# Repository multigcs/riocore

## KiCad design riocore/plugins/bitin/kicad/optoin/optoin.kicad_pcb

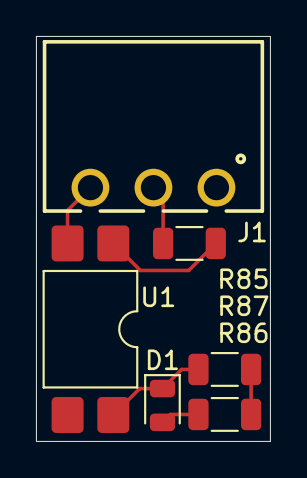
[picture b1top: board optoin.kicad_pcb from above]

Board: 2 copper layers, 13.0 x 22.5 mm, 6 parts (0 on the bottom side), 6 nets.

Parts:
D1: LED; LED_0805_2012Metric
J1: opto_in; 691322110003
R85: 3k3; R_1206_3216Metric
R86: 560; R_1206_3216Metric
R87: 1k; R_1206_3216Metric
U1: LTV-817S; SMDIP-4_W9.53mm

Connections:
+3V3: R86.1, R87.1
/bit: D1.1 (K), R87.2, U1.4
F_GND: J1.3, U1.2
unnamed: D1.2 (A), R86.2
unnamed: J1.2, R85.2
unnamed: R85.1, U1.1

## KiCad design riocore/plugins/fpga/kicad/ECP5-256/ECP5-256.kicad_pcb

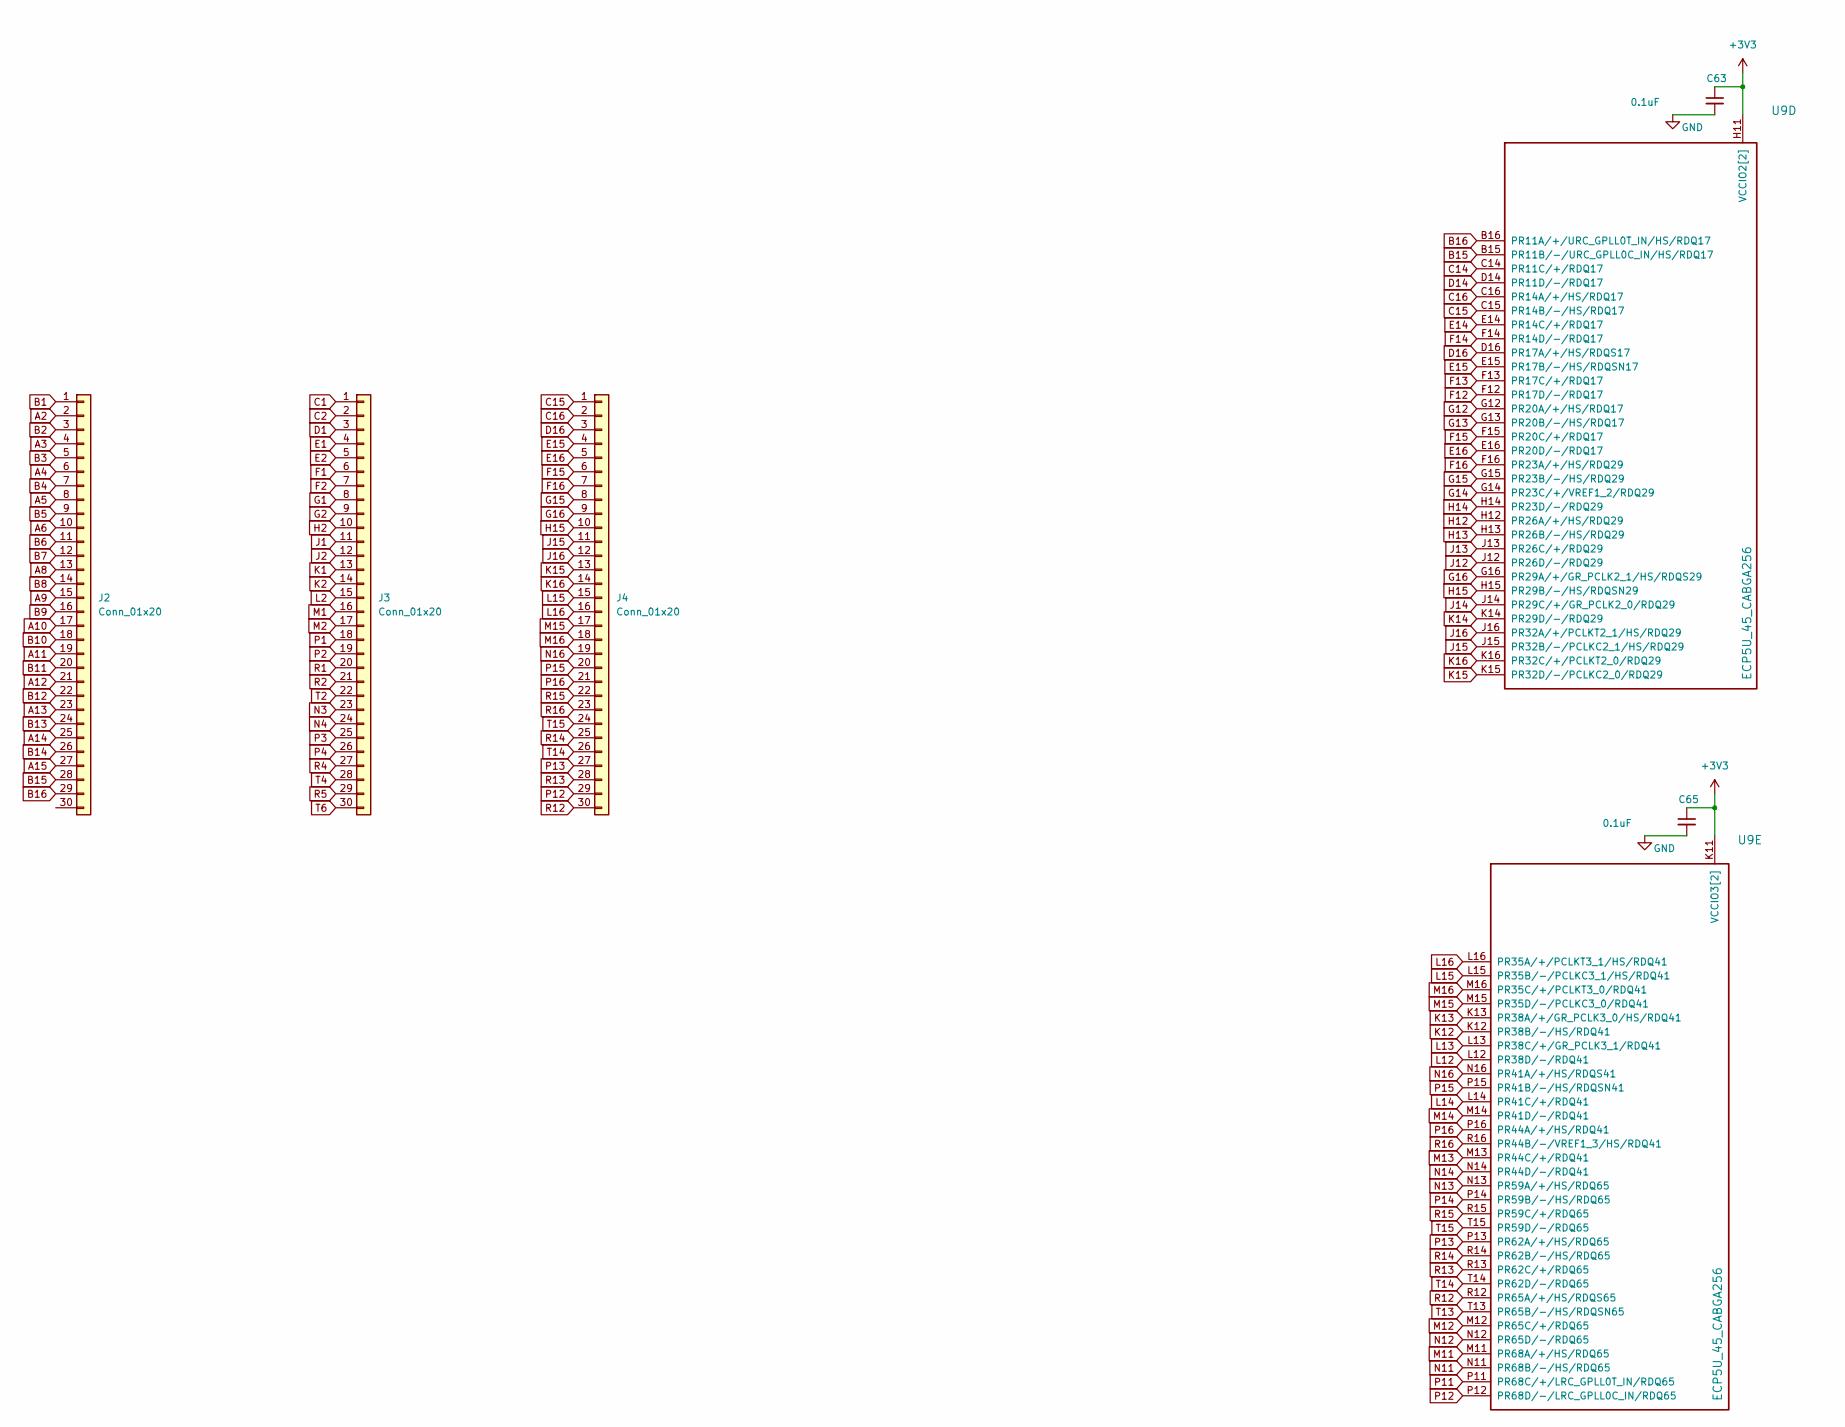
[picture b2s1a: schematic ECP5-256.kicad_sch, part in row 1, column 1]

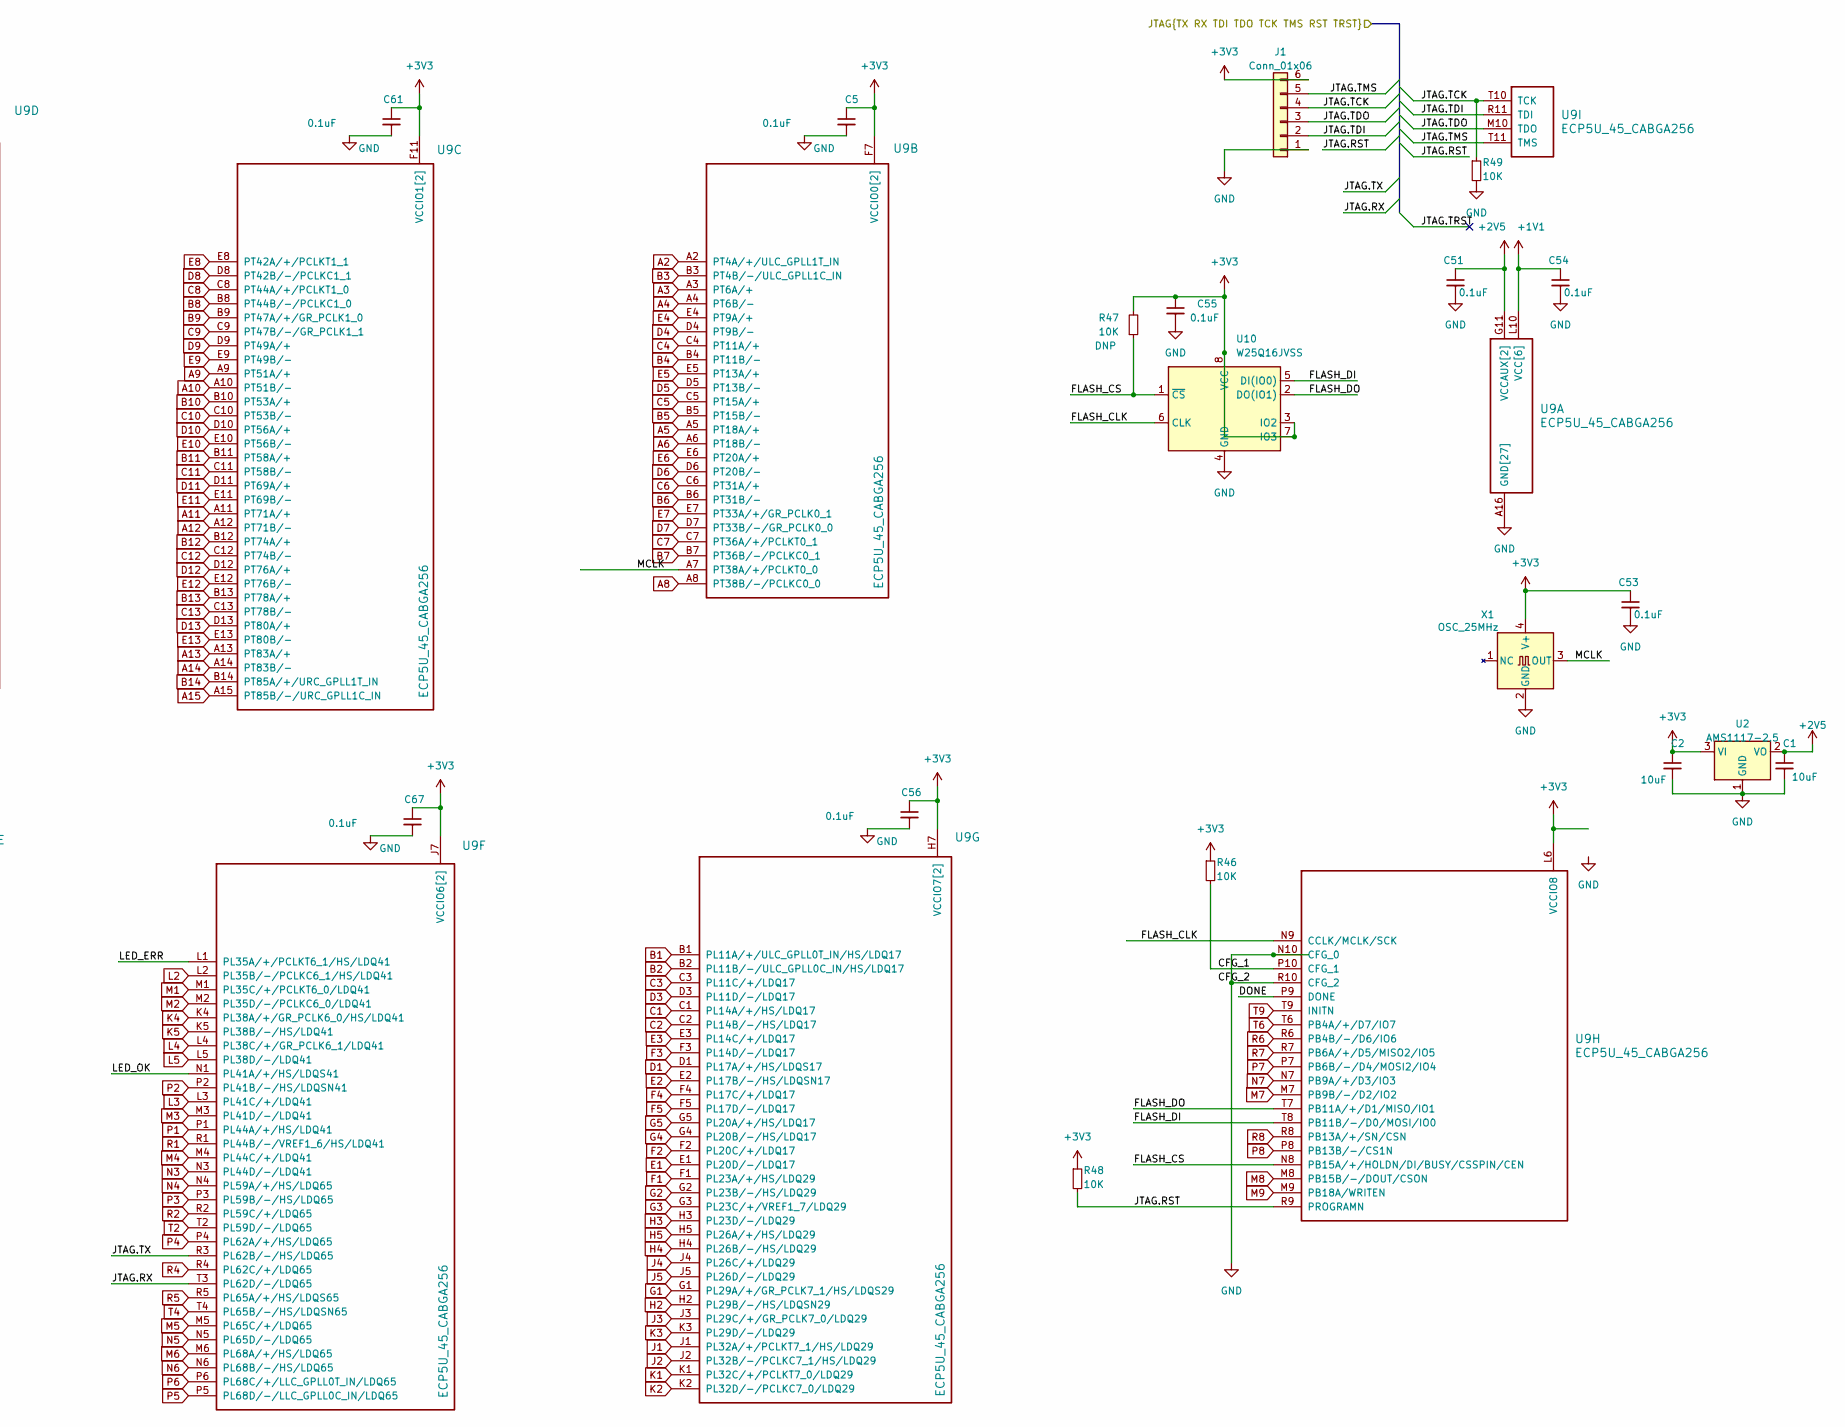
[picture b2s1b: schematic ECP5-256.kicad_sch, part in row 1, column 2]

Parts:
C1, C2: 10uF; C_0805_2012Metric; LCSC# C56392
C5, C51, C53, C54, C56, C61, C63, C65, C67: 0.1uF; C_0805_2012Metric; LCSC# C56392
C55: 0.1uF; C_0805_2012Metric; MPN CC0603KRX7R9BB104; LCSC# C14663
J1: Conn_01x06; PinHeader_1x06_P2.54mm_Vertical
J2, J3, J4: Conn_01x20; PinHeader_1x30_P1.27mm_Vertical
R46, R48, R49: 10K; R_0603_1608Metric; LCSC# C98220
R47: 10K; R_0603_1608Metric; MPN RC0603FR-0710KL; LCSC# C98220
U2: AMS1117-2.5; SOT-223-3_TabPin2
U9: ECP5U_45_CABGA256; BGA-256_14.0x14.0mm_Layout16x16_P0.8mm_Ball0.45mm_Pad0.32mm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; MPN LFE5U-12F-6BG256C; LCSC# C1550762
U10: W25Q16JVSS; SOIC-8_5.3x5.3mm_P1.27mm; MPN W25Q16JVSSIQ; LCSC# C82317
X1: OSC_25MHz; Oscillator_SMD_EuroQuartz_XO32-4Pin_3.2x2.5mm; MPN OT322525MJBA4SL; LCSC# C669088

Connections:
+1V1: C54.1, U9.G6 (VCC[6]), U9.G7 (VCC[6]), U9.G9 (VCC[6]), U9.L8 (VCC[6]), U9.L9 (VCC[6]), U9.L10 (VCC[6])
+2V5: C1.1, C51.1, U2.2 (VO), U9.G11 (VCCAUX[2]), U9.L7 (VCCAUX[2])
+3V3: C2.1, C5.1, C53.1, C55.1, C56.1, C61.1, C63.1, C65.1, C67.1, J1.6, R46.1, R47.2, R48.1, U2.3 (VI), U9.F6 (VCCIO0[2]), U9.F7 (VCCIO0[2]), U9.F10 (VCCIO1[2]), U9.F11 (VCCIO1[2]), U9.H6 (VCCIO7[2]), U9.H7 (VCCIO7[2]), U9.H11 (VCCIO2[2]), U9.J6 (VCCIO6[2]), U9.J7 (VCCIO6[2]), U9.J11 (VCCIO2[2]), U9.K11 (VCCIO3[2]), U9.L6 (VCCIO8), U9.L11 (VCCIO3[2]), U10.3 (IO2), U10.7 (IO3), U10.8 (VCC), X1.4 (V+)
/CFG_1: R46.2, U9.P10 (CFG_1)
/DONE: U9.P9 (DONE)
/FLASH_CLK: U9.N9 (CCLK/MCLK/SCK), U10.6 (CLK)
/FLASH_CS: R47.1, U9.N8 (PB15A/+/HOLDN/DI/BUSY/CSSPIN/CEN), U10.1 (~CS)
/FLASH_DI: U9.T8 (PB11B/-/D0/MOSI/IO0), U10.5 (DI(IO0))
/FLASH_DO: U9.T7 (PB11A/+/D1/MISO/IO1), U10.2 (DO(IO1))
/JTAG.RST: R48.2, U9.R9 (PROGRAMN)
/JTAG.RX: U9.T3 (PL62D/-/LDQ65)
/JTAG.TCK: J1.4, R49.1, U9.T10 (TCK)
/JTAG.TDI: J1.2, U9.R11 (TDI)
/JTAG.TDO: J1.3, U9.M10 (TDO)
/JTAG.TMS: J1.5, U9.T11 (TMS)
/JTAG.TX: U9.R3 (PL62B/-/HS/LDQ65)
/LED_ERR: U9.L1 (PL35A/+/PCLKT6_1/HS/LDQ41)
/LED_OK: U9.N1 (PL41A/+/HS/LDQS41)
/MCLK: U9.A7 (PT38A/+/PCLKT0_0), X1.3 (OUT)
A2: J2.2, U9.A2 (PT4A/+/ULC_GPLL1T_IN)
A3: J2.4, U9.A3 (PT6A/+)
A4: J2.6, U9.A4 (PT6B/-)
A5: J2.8, U9.A5 (PT18A/+)
A6: J2.10, U9.A6 (PT18B/-)
A8: J2.13, U9.A8 (PT38B/-/PCLKC0_0)
A9: J2.15, U9.A9 (PT51A/+)
A10: J2.17, U9.A10 (PT51B/-)
A11: J2.19, U9.A11 (PT71A/+)
A12: J2.21, U9.A12 (PT71B/-)
A13: J2.23, U9.A13 (PT83A/+)
A14: J2.25, U9.A14 (PT83B/-)
A15: J2.27, U9.A15 (PT85B/-/URC_GPLL1C_IN)
B1: J2.1, U9.B1 (PL11A/+/ULC_GPLL0T_IN/HS/LDQ17)
B2: J2.3, U9.B2 (PL11B/-/ULC_GPLL0C_IN/HS/LDQ17)
B3: J2.5, U9.B3 (PT4B/-/ULC_GPLL1C_IN)
B4: J2.7, U9.B4 (PT11B/-)
B5: J2.9, U9.B5 (PT15B/-)
B6: J2.11, U9.B6 (PT31B/-)
B7: J2.12, U9.B7 (PT36B/-/PCLKC0_1)
B8: J2.14, U9.B8 (PT44B/-/PCLKC1_0)
B9: J2.16, U9.B9 (PT47A/+/GR_PCLK1_0)
B10: J2.18, U9.B10 (PT53A/+)
B11: J2.20, U9.B11 (PT58A/+)
B12: J2.22, U9.B12 (PT74A/+)
B13: J2.24, U9.B13 (PT78A/+)
B14: J2.26, U9.B14 (PT85A/+/URC_GPLL1T_IN)
B15: J2.28, U9.B15 (PR11B/-/URC_GPLL0C_IN/HS/RDQ17)
B16: J2.29, U9.B16 (PR11A/+/URC_GPLL0T_IN/HS/RDQ17)
C1: J3.1, U9.C1 (PL14A/+/HS/LDQ17)
C2: J3.2, U9.C2 (PL14B/-/HS/LDQ17)
C3: U9.C3 (PL11C/+/LDQ17)
C4: U9.C4 (PT11A/+)
C5: U9.C5 (PT15A/+)
C6: U9.C6 (PT31A/+)
C7: U9.C7 (PT36A/+/PCLKT0_1)
C8: U9.C8 (PT44A/+/PCLKT1_0)
C9: U9.C9 (PT47B/-/GR_PCLK1_1)
C10: U9.C10 (PT53B/-)
C11: U9.C11 (PT58B/-)
C12: U9.C12 (PT74B/-)
C13: U9.C13 (PT78B/-)
C14: U9.C14 (PR11C/+/RDQ17)
C15: J4.1, U9.C15 (PR14B/-/HS/RDQ17)
C16: J4.2, U9.C16 (PR14A/+/HS/RDQ17)
D1: J3.3, U9.D1 (PL17A/+/HS/LDQS17)
D3: U9.D3 (PL11D/-/LDQ17)
D4: U9.D4 (PT9B/-)
D5: U9.D5 (PT13B/-)
D6: U9.D6 (PT20B/-)
D7: U9.D7 (PT33B/-/GR_PCLK0_0)
D8: U9.D8 (PT42B/-/PCLKC1_1)
D9: U9.D9 (PT49A/+)
D10: U9.D10 (PT56A/+)
D11: U9.D11 (PT69A/+)
D12: U9.D12 (PT76A/+)
D13: U9.D13 (PT80A/+)
D14: U9.D14 (PR11D/-/RDQ17)
D16: J4.3, U9.D16 (PR17A/+/HS/RDQS17)
E1: J3.4, U9.E1 (PL20D/-/LDQ17)
E2: J3.5, U9.E2 (PL17B/-/HS/LDQSN17)
E3: U9.E3 (PL14C/+/LDQ17)
E4: U9.E4 (PT9A/+)
E5: U9.E5 (PT13A/+)
E6: U9.E6 (PT20A/+)
E7: U9.E7 (PT33A/+/GR_PCLK0_1)
E8: U9.E8 (PT42A/+/PCLKT1_1)
E9: U9.E9 (PT49B/-)
E10: U9.E10 (PT56B/-)
E11: U9.E11 (PT69B/-)
E12: U9.E12 (PT76B/-)
E13: U9.E13 (PT80B/-)
E14: U9.E14 (PR14C/+/RDQ17)
E15: J4.4, U9.E15 (PR17B/-/HS/RDQSN17)
E16: J4.5, U9.E16 (PR20D/-/RDQ17)
F1: J3.6, U9.F1 (PL23A/+/HS/LDQ29)
F2: J3.7, U9.F2 (PL20C/+/LDQ17)
F3: U9.F3 (PL14D/-/LDQ17)
F4: U9.F4 (PL17C/+/LDQ17)
F5: U9.F5 (PL17D/-/LDQ17)
F12: U9.F12 (PR17D/-/RDQ17)
F13: U9.F13 (PR17C/+/RDQ17)
F14: U9.F14 (PR14D/-/RDQ17)
F15: J4.6, U9.F15 (PR20C/+/RDQ17)
F16: J4.7, U9.F16 (PR23A/+/HS/RDQ29)
G1: J3.8, U9.G1 (PL29A/+/GR_PCLK7_1/HS/LDQS29)
G2: J3.9, U9.G2 (PL23B/-/HS/LDQ29)
G3: U9.G3 (PL23C/+/VREF1_7/LDQ29)
G4: U9.G4 (PL20B/-/HS/LDQ17)
G5: U9.G5 (PL20A/+/HS/LDQ17)
G12: U9.G12 (PR20A/+/HS/RDQ17)
G13: U9.G13 (PR20B/-/HS/RDQ17)
G14: U9.G14 (PR23C/+/VREF1_2/RDQ29)
G15: J4.8, U9.G15 (PR23B/-/HS/RDQ29)
G16: J4.9, U9.G16 (PR29A/+/GR_PCLK2_1/HS/RDQS29)
GND: C1.2, C2.2, C5.2, C51.2, C53.2, C54.2, C55.2, C56.2, C61.2, C63.2, C65.2, C67.2, J1.1, R49.2, U2.1 (GND), U9.A1 (GND[27]), U9.A16 (GND[27]), U9.D2 (GND[27]), U9.D15 (GND[27]), U9.F8 (GND[27]), U9.F9 (GND[27]), U9.G8 (GND[27]), U9.G10 (GND[27]), U9.H1 (GND[27]), U9.H8 (GND[27]), U9.H9 (GND[27]), U9.H10 (GND[27]), U9.H16 (GND[27]), U9.J8 (GND[27]), U9.J9 (GND[27]), U9.J10 (GND[27]), U9.K6 (GND[27]), U9.K7 (GND[27]), U9.K8 (GND[27]), U9.K9 (GND[27]), U9.K10 (GND[27]), U9.N2 (GND[27]), U9.N10 (CFG_0), U9.N15 (GND[27]), U9.R10 (CFG_2), U9.T1 (GND[27]), U9.T5 (GND[27]), U9.T12 (GND[27]), U9.T16 (GND[27]), U10.4 (GND), X1.2 (GND)
H2: J3.10, U9.H2 (PL29B/-/HS/LDQSN29)
H3: U9.H3 (PL23D/-/LDQ29)
H4: U9.H4 (PL26B/-/HS/LDQ29)
H5: U9.H5 (PL26A/+/HS/LDQ29)
H12: U9.H12 (PR26A/+/HS/RDQ29)
H13: U9.H13 (PR26B/-/HS/RDQ29)
H14: U9.H14 (PR23D/-/RDQ29)
H15: J4.10, U9.H15 (PR29B/-/HS/RDQSN29)
J1: J3.11, U9.J1 (PL32A/+/PCLKT7_1/HS/LDQ29)
J2: J3.12, U9.J2 (PL32B/-/PCLKC7_1/HS/LDQ29)
J3: U9.J3 (PL29C/+/GR_PCLK7_0/LDQ29)
J4: U9.J4 (PL26C/+/LDQ29)
J5: U9.J5 (PL26D/-/LDQ29)
J12: U9.J12 (PR26D/-/RDQ29)
J13: U9.J13 (PR26C/+/RDQ29)
J14: U9.J14 (PR29C/+/GR_PCLK2_0/RDQ29)
J15: J4.11, U9.J15 (PR32B/-/PCLKC2_1/HS/RDQ29)
J16: J4.12, U9.J16 (PR32A/+/PCLKT2_1/HS/RDQ29)
K1: J3.13, U9.K1 (PL32C/+/PCLKT7_0/LDQ29)
K2: J3.14, U9.K2 (PL32D/-/PCLKC7_0/LDQ29)
K3: U9.K3 (PL29D/-/LDQ29)
K4: U9.K4 (PL38A/+/GR_PCLK6_0/HS/LDQ41)
K5: U9.K5 (PL38B/-/HS/LDQ41)
K12: U9.K12 (PR38B/-/HS/RDQ41)
K13: U9.K13 (PR38A/+/GR_PCLK3_0/HS/RDQ41)
K14: U9.K14 (PR29D/-/RDQ29)
K15: J4.13, U9.K15 (PR32D/-/PCLKC2_0/RDQ29)
K16: J4.14, U9.K16 (PR32C/+/PCLKT2_0/RDQ29)
L2: J3.15, U9.L2 (PL35B/-/PCLKC6_1/HS/LDQ41)
L3: U9.L3 (PL41C/+/LDQ41)
L4: U9.L4 (PL38C/+/GR_PCLK6_1/LDQ41)
L5: U9.L5 (PL38D/-/LDQ41)
L12: U9.L12 (PR38D/-/RDQ41)
L13: U9.L13 (PR38C/+/GR_PCLK3_1/RDQ41)
L14: U9.L14 (PR41C/+/RDQ41)
L15: J4.15, U9.L15 (PR35B/-/PCLKC3_1/HS/RDQ41)
L16: J4.16, U9.L16 (PR35A/+/PCLKT3_1/HS/RDQ41)
M1: J3.16, U9.M1 (PL35C/+/PCLKT6_0/LDQ41)
M2: J3.17, U9.M2 (PL35D/-/PCLKC6_0/LDQ41)
M3: U9.M3 (PL41D/-/LDQ41)
M4: U9.M4 (PL44C/+/LDQ41)
M5: U9.M5 (PL65C/+/LDQ65)
M6: U9.M6 (PL68A/+/HS/LDQ65)
M7: U9.M7 (PB9B/-/D2/IO2)
M8: U9.M8 (PB15B/-/DOUT/CSON)
M9: U9.M9 (PB18A/WRITEN)
M11: U9.M11 (PR68A/+/HS/RDQ65)
M12: U9.M12 (PR65C/+/RDQ65)
M13: U9.M13 (PR44C/+/RDQ41)
M14: U9.M14 (PR41D/-/RDQ41)
M15: J4.17, U9.M15 (PR35D/-/PCLKC3_0/RDQ41)
M16: J4.18, U9.M16 (PR35C/+/PCLKT3_0/RDQ41)
N3: J3.23, U9.N3 (PL44D/-/LDQ41)
N4: J3.24, U9.N4 (PL59A/+/HS/LDQ65)
N5: U9.N5 (PL65D/-/LDQ65)
N6: U9.N6 (PL68B/-/HS/LDQ65)
N7: U9.N7 (PB9A/+/D3/IO3)
N11: U9.N11 (PR68B/-/HS/RDQ65)
N12: U9.N12 (PR65D/-/RDQ65)
N13: U9.N13 (PR59A/+/HS/RDQ65)
N14: U9.N14 (PR44D/-/RDQ41)
N16: J4.19, U9.N16 (PR41A/+/HS/RDQS41)
P1: J3.18, U9.P1 (PL44A/+/HS/LDQ41)
P2: J3.19, U9.P2 (PL41B/-/HS/LDQSN41)
P3: J3.25, U9.P3 (PL59B/-/HS/LDQ65)
P4: J3.26, U9.P4 (PL62A/+/HS/LDQ65)
P5: U9.P5 (PL68D/-/LLC_GPLL0C_IN/LDQ65)
P6: U9.P6 (PL68C/+/LLC_GPLL0T_IN/LDQ65)
P7: U9.P7 (PB6B/-/D4/MOSI2/IO4)
P8: U9.P8 (PB13B/-/CS1N)
P11: U9.P11 (PR68C/+/LRC_GPLL0T_IN/RDQ65)
P12: J4.29, U9.P12 (PR68D/-/LRC_GPLL0C_IN/RDQ65)
P13: J4.27, U9.P13 (PR62A/+/HS/RDQ65)
P14: U9.P14 (PR59B/-/HS/RDQ65)
P15: J4.20, U9.P15 (PR41B/-/HS/RDQSN41)
P16: J4.21, U9.P16 (PR44A/+/HS/RDQ41)
R1: J3.20, U9.R1 (PL44B/-/VREF1_6/HS/LDQ41)
R2: J3.21, U9.R2 (PL59C/+/LDQ65)
R4: J3.27, U9.R4 (PL62C/+/LDQ65)
R5: J3.29, U9.R5 (PL65A/+/HS/LDQS65)
R6: U9.R6 (PB4B/-/D6/IO6)
R7: U9.R7 (PB6A/+/D5/MISO2/IO5)
R8: U9.R8 (PB13A/+/SN/CSN)
R12: J4.30, U9.R12 (PR65A/+/HS/RDQS65)
R13: J4.28, U9.R13 (PR62C/+/RDQ65)
R14: J4.25, U9.R14 (PR62B/-/HS/RDQ65)
R15: J4.22, U9.R15 (PR59C/+/RDQ65)
R16: J4.23, U9.R16 (PR44B/-/VREF1_3/HS/RDQ41)
T2: J3.22, U9.T2 (PL59D/-/LDQ65)
T4: J3.28, U9.T4 (PL65B/-/HS/LDQSN65)
T6: J3.30, U9.T6 (PB4A/+/D7/IO7)
T9: U9.T9 (INITN)
T13: U9.T13 (PR65B/-/HS/RDQSN65)
T14: J4.26, U9.T14 (PR62D/-/RDQ65)
T15: J4.24, U9.T15 (PR59D/-/RDQ65)

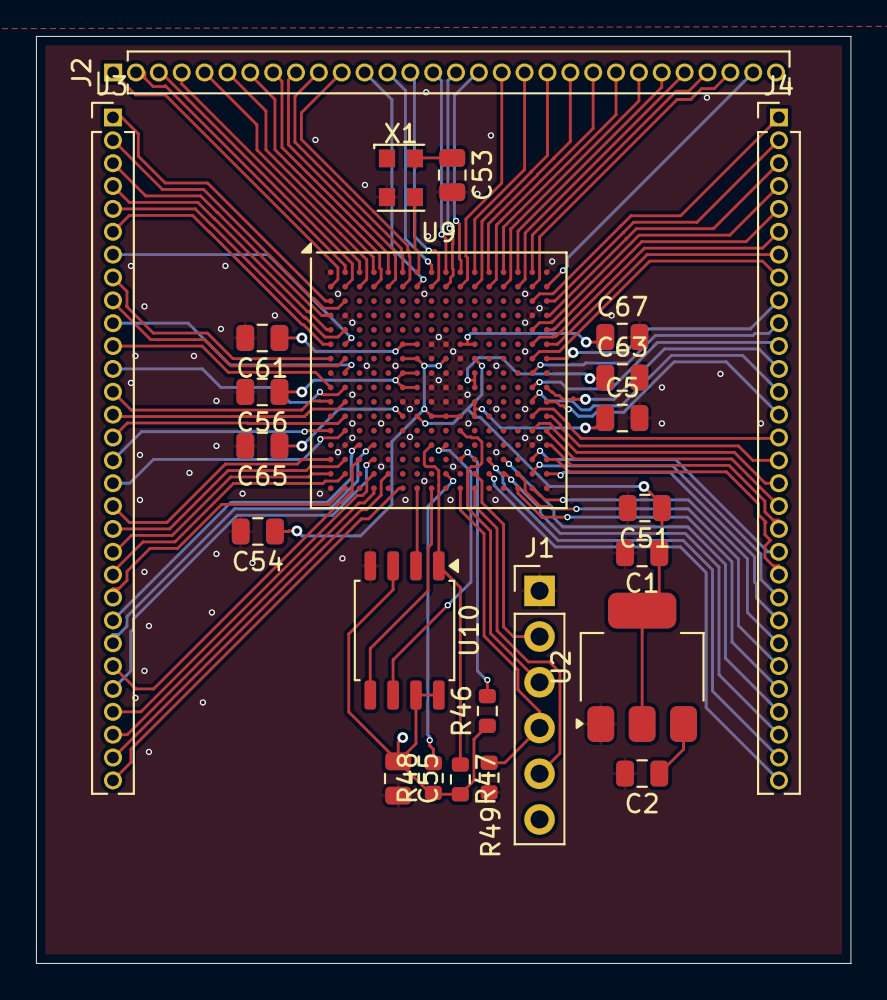
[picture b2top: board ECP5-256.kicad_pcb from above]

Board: 2 copper layers, 45.2 x 51.5 mm, 24 parts (0 on the bottom side), 104 nets.

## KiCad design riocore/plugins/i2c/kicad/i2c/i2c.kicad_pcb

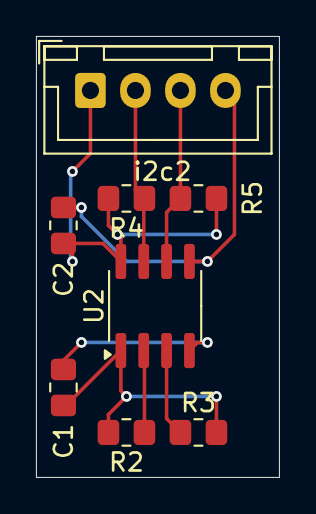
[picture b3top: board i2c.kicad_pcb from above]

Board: 2 copper layers, 13.5 x 24.5 mm, 8 parts (0 on the bottom side), 8 nets.

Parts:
C1, C2: 100n; R_0805_2012Metric_Pad1.20x1.40mm_HandSolder
R2, R3, R4, R5: 4k7; R_0805_2012Metric_Pad1.20x1.40mm_HandSolder
U2: ISO1540; SOIC-8_3.9x4.9mm_P1.27mm
i2c2: Conn_01x04; JST_XH_B4B-XH-A_1x04_P2.50mm_Vertical

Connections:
3V3: R2.2, R3.2, U2.1 (VCC1)
/scl: R3.1, U2.3 (SCL1)
/sda: R2.1, U2.2 (SDA1)
F_5V: C2.1, R4.2, R5.2, U2.8 (VCC2), i2c2.1
F_GND: C2.2, U2.5 (GND2), i2c2.4
GND: C1.2, U2.4 (GND1)
unnamed: R5.1, U2.6 (SCL2), i2c2.3
unnamed: R4.1, U2.7 (SDA2), i2c2.2

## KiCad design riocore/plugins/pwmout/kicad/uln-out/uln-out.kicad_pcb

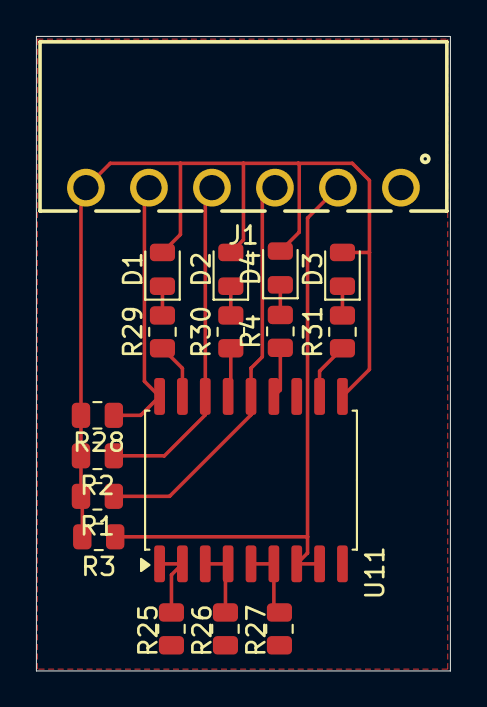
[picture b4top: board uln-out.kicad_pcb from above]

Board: 2 copper layers, 23.0 x 35.2 mm, 17 parts (0 on the bottom side), 17 nets.

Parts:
D1, D2, D3, D4: LED; LED_0805_2012Metric
J1: pwmout; 691322110006
R1, R2, R3, R25, R26, R27, R28: 10k; R_0805_2012Metric
R4, R29, R30, R31: 1k; R_0805_2012Metric
U11: ULN2803A; SOIC-18W_7.5x11.6mm_P1.27mm

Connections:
+5V: D1.2 (A), D2.2 (A), D3.2 (A), D4.2 (A), J1.6, R1.2, R2.2, R3.2, R28.2, U11.10 (COM)
/dir: R26.2, U11.3 (I3), U11.4 (I4)
/en: R27.2, U11.5 (I5), U11.6 (I6)
/pwm: R25.2, U11.1 (I1), U11.2 (I2)
GND: J1.1, R25.1, R26.1, R27.1, U11.9 (GND)
unnamed: D1.1 (K), R29.2
unnamed: D2.1 (K), R30.2
unnamed: D3.1 (K), R31.2
unnamed: D4.1 (K), R4.2
unnamed: J1.2, R3.1, U11.7 (I7), U11.8 (I8)
unnamed: J1.5, R28.1, U11.18 (O1)
unnamed: R29.1, U11.17 (O2)
unnamed: J1.4, R2.1, U11.16 (O3)
unnamed: R30.1, U11.15 (O4)
unnamed: J1.3, R1.1, U11.14 (O5)
unnamed: R4.1, U11.13 (O6)
unnamed: R31.1, U11.11 (O8)

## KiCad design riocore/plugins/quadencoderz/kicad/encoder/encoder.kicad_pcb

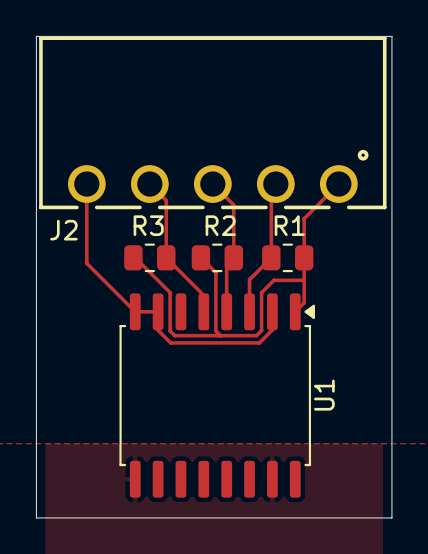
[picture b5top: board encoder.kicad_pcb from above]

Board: 2 copper layers, 19.8 x 26.8 mm, 5 parts (0 on the bottom side), 7 nets.

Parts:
J2: 691322110005
R1, R2, R3: 10k; R_0805_2012Metric
U1: ADuM1411; SOIC-16W_7.5x10.3mm_P1.27mm

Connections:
+3.3V: U1.11 (VID), U1.16 (VDD2)
F_5V: J2.1, R1.2, R2.2, R3.2, U1.1 (VDD1)
F_GND: J2.5, U1.2 (GND1), U1.7 (CTRL1), U1.8 (GND1)
GND: U1.9 (GND2), U1.15 (GND2)
unnamed: J2.2, R1.1, U1.3 (VIA)
unnamed: J2.3, R2.1, U1.4 (VIB)
unnamed: J2.4, R3.1, U1.5 (VIC)
